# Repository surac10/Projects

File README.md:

# Projects
My treasure cove of projects, both in-school and personal!

### Electrical Projects
1. [Boost Converter](./electrical_projects/boost_converter): Final project for **Applied Circuits**; 5 V $\rightarrow$ 12 V converter.

2. [Frequency Analyzer](./electrical_projects/frequency_analyzer): Semester-long project for **Electronics**; identifies frequency ranges in audio signals.

3. [Star PCB](./electrical_projects/star_keychain_pcb): First independently designed PCB: a custom star-shaped board.

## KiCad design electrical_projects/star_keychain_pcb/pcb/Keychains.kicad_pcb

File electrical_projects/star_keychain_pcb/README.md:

# Star Keychain PCB

## Overview
A custom star-shaped PCB keychain designed in KiCad as a gift for my younger sisters. This was my first independently designed PCB, taking the project from schematic drawing to PCB layout, manufacturing, soldering, and testing. I included the schematic, PCB, and a zip containing the Gerber files in their respective folders for reference.

## Features 
- Single-layer PCB designed in KiCad with a copper ground plane.
- 5 LEDs, each driven by its own 200 $\Omega$ current-limiting resistor.
- Powered by a CR2032 3 V coin cell.
- Pushbutton switch controls power to all LEDs.
- Estimated battery life of approximately 8-9 hours under continuous operation.

### Specifications
| Specification | Value |
| :------------ | :---: |
| Software      | KiCad |
| PCB Layers    | 1     |
| PCB Size      | ~ 3 x 3 in |
| Power Source  | CR2032 |
| LEDs          | 5     |
| Resistors     | 5 x 200 $\Omega$ |
| Manufacturing | JLCPCB |
| Components    | DigiKey |

## Highlights
- Designing a PCB from a schematic using KiCad.
- Learned PCB layout fundamentals including trace routing, copper pours, footprints, and design rule checking.
  - Creating and importing custom silkscreen artwork.
- Generating Gerber files and verifying manufacturability before fabrication via [FreeDFM](https://www.my4pcb.com/net35/FreeDFMNet/FreeDFMHome.aspx).
  - Encountered manufacturability check issues while validating the Gerber files using FreeDFM. After regenerating the Gerbers and verifying the export settings, the design passed all manufacturing checks.
- Ordered fabricated PCBs from [JLCPCB](https://jlcpcb.com/) and sourced components from [DigiKey](https://www.digikey.com/).

## Images

### Schematic

### PCB Layout

### Finished PCB

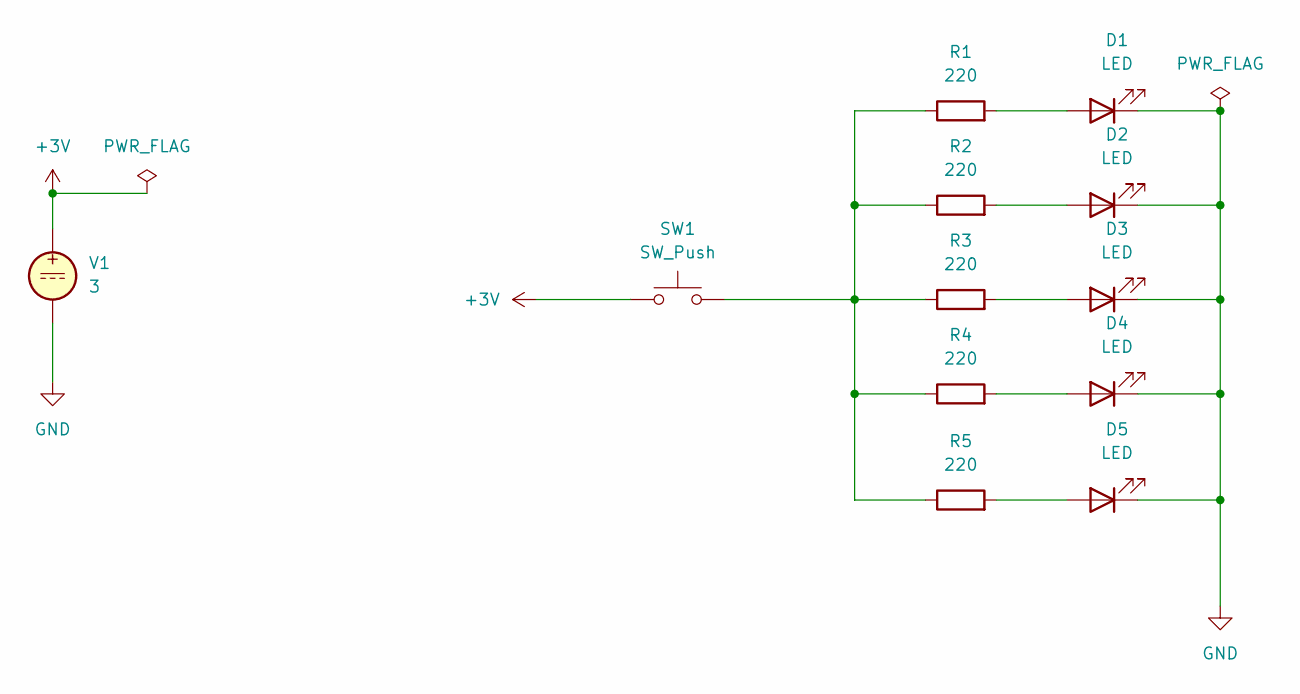
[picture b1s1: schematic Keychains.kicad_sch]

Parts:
D1, D2, D3, D4, D5: LED; LED_D3.0mm
R1, R2, R3, R4, R5: 220; R_Axial_DIN0309_L9.0mm_D3.2mm_P12.70mm_Horizontal
SW1: SW_Push; SW_PUSH_6mm
V1: 3; BatteryHolder_MYOUNG_BS-07-A1BJ001_CR2032

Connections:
+3V: SW1.1, V1.1
GND: D1.1 (K), D2.1 (K), D3.1 (K), D4.1 (K), D5.1 (K), V1.2
unnamed: D1.2 (A), R1.2
unnamed: D2.2 (A), R2.2
unnamed: D3.2 (A), R3.2
unnamed: D4.2 (A), R4.2
unnamed: D5.2 (A), R5.2
unnamed: R1.1, R2.1, R3.1, R4.1, R5.1, SW1.2

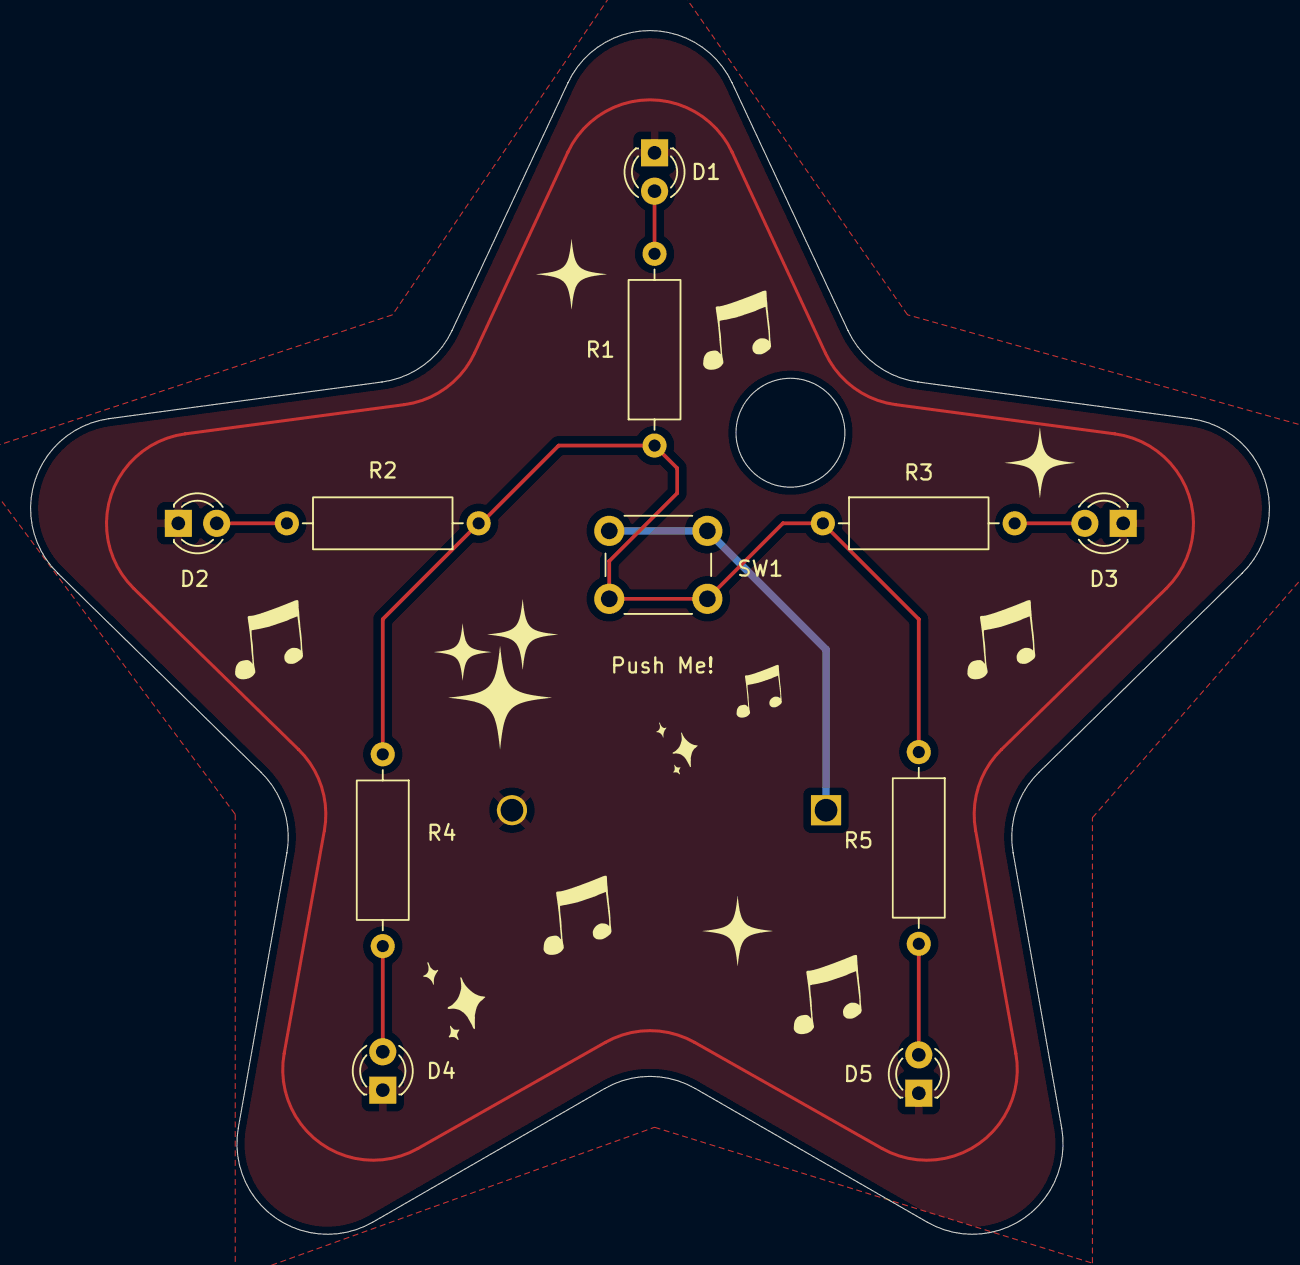
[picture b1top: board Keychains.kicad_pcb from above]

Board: 2 copper layers, 82.0 x 79.7 mm, 12 parts (1 on the bottom side), 8 nets.
